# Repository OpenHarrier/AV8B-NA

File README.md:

# AV8B-NA
Files for the AV-8B N/A

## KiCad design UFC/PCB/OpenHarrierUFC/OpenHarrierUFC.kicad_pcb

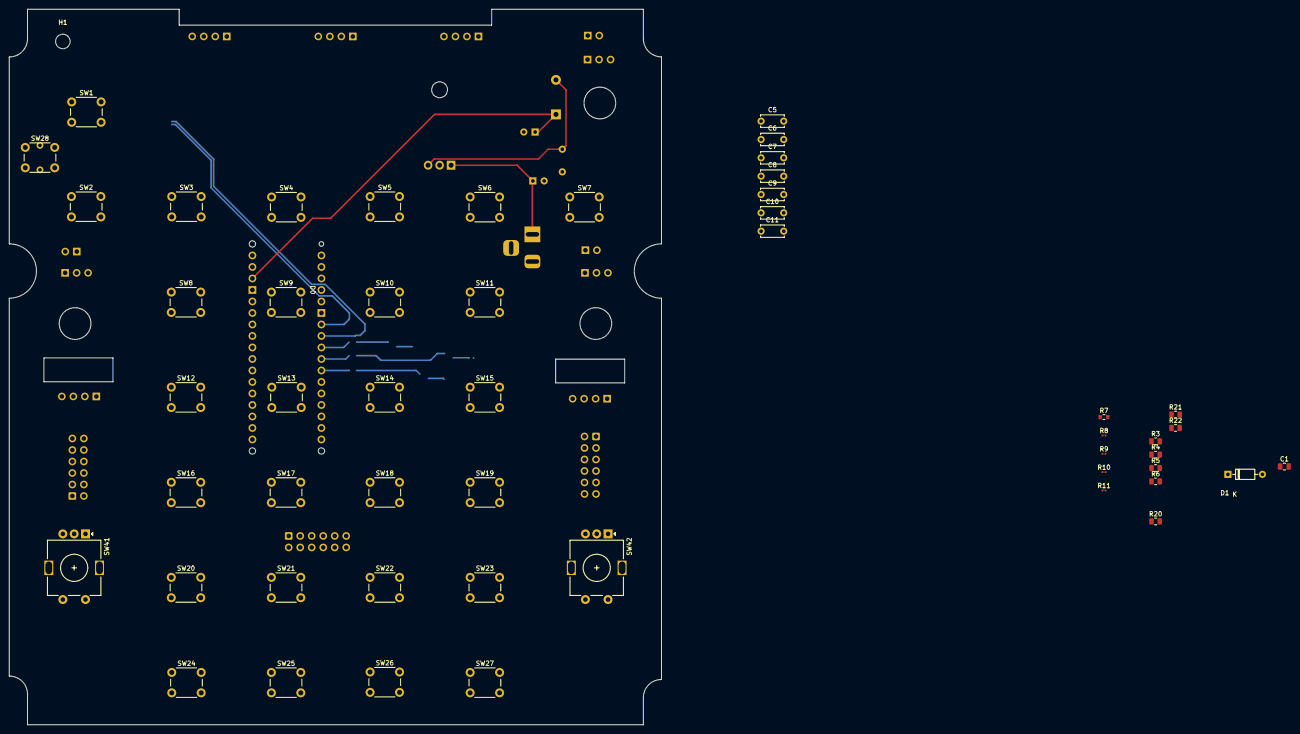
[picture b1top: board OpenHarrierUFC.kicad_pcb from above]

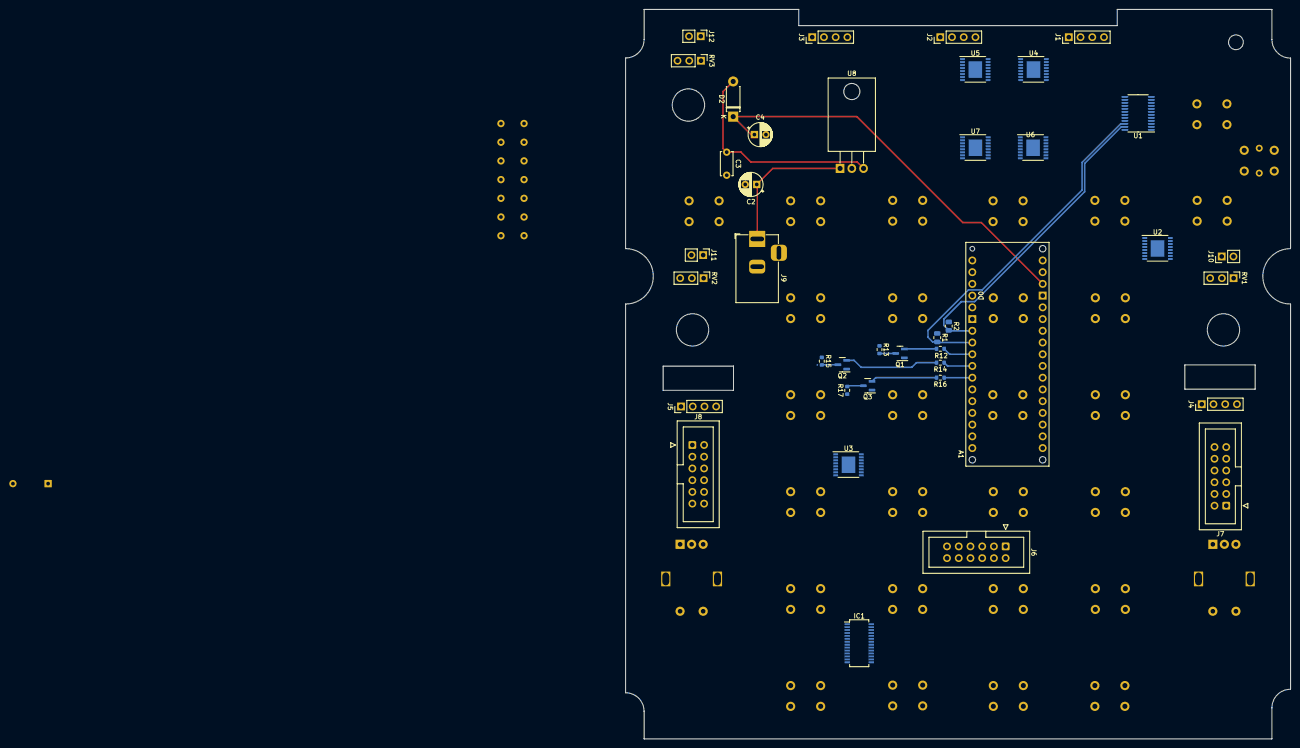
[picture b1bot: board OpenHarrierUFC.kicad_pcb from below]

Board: 2 copper layers, 144.0 x 158.0 mm, 92 parts (40 on the bottom side), 97 nets.

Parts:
A1: Arduino_Micro_Socket
C1: 10uF; C_0805_2012Metric
C2, C4: 100 uF; CP_Radial_D5.0mm_P2.50mm
C3, C5, C6, C7, C8, C9, C10, C11: 100 nF; C_Disc_D5.0mm_W2.5mm_P5.00mm
D1: 1N4148; D_DO-35_SOD27_P7.62mm_Horizontal
D2: 1N5819; D_DO-41_SOD81_P7.62mm_Horizontal
H1: MountingHole; MountingHole_3.2mm_M3
IC1: HT16K33-28SOP; SSOP-28_3.9x9.9mm_P0.635mm
J1: SCRATCHPAD1; PinHeader_1x04_P2.54mm_Vertical
J2: SCRATCHPAD2; PinHeader_1x04_P2.54mm_Vertical
J3: SCRATCHPAD3; PinHeader_1x04_P2.54mm_Vertical
J4, J5: Conn_01x04_Pin; PinHeader_1x04_P2.54mm_Vertical
J6: HUD PANEL; IDC-Header_2x06_P2.54mm_Vertical
J7: LEFT ANNUN; IDC-Header_2x06_P2.54mm_Vertical
J8: RIGHT ANNUN; IDC-Header_2x06_P2.54mm_Vertical
J9: Barrel_Jack_Switch; BarrelJack_Horizontal
J10: COMM1 ON/OFF; PinHeader_1x02_P2.54mm_Vertical
J11: COMM2 ON/OFF; PinHeader_1x02_P2.54mm_Vertical
J12: SCRTCH ON/OFF; PinHeader_1x02_P2.54mm_Vertical
Q1, Q2, Q3: 2N3904; SOT-23
R1, R2, R4, R5, R6: 10k; R_0805_2012Metric
R3: R; R_0805_2012Metric
R7: 2k2; R_0603_1608Metric
R8, R9, R10, R11: 2k2; R_0201_0603Metric
R12, R14, R16: 10k; R_0603_1608Metric
R13, R15, R17: 1k; R_0603_1608Metric
R20, R21, R22: 47K; R_0805_2012Metric
RV1, RV2, RV3: 10k; PinHeader_1x03_P2.54mm_Vertical
SW1, SW2, SW3, SW4, SW5, SW6, SW7, SW8, SW9, SW10, SW11, SW12, SW13, SW14, SW15, SW16, SW17, SW18, SW19, SW20, SW21, SW22, SW23, SW24, SW25, SW26, SW27: SW_Push; SW_PUSH_6mm
SW28: SW_Push_LED; SW_PUSH_6mm
SW41: COMM1 Encoder; RotaryEncoder_Alps_EC11E-Switch_Vertical_H20mm
SW42: COMM2 Encoder; RotaryEncoder_Alps_EC11E-Switch_Vertical_H20mm
U1: TCA9548APWR; TSSOP-24_4.4x7.8mm_P0.65mm
U2, U3, U4, U5, U6, U7: 4051; TSSOP-16-1EP_4.4x5mm_P0.65mm
U8: LM7805_TO220; TO-220-3_Horizontal_TabDown

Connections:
+3V3: R7.1, R8.1, R9.1, R10.1, R11.1
+5V: A1.VIN, C4.1, C5.1, C6.1, C7.1, C8.1, C9.1, C10.1, C11.1, D2.1 (K), IC1.28 (VDD), R13.1, R15.1, R17.1, U2.16 (VDD), U3.16 (VDD), U4.16 (VDD), U5.16 (VDD), U6.16 (VDD), U7.16 (VDD)
ADC0: A1.A0, U7.3 (X)
ADC_BRT: J6.3, U7.1 (X4)
ADC_CON: J6.4, U7.2 (X6)
ADC_SYM: J6.1, U7.12 (X3)
BUTTON1: A1.D7 (D7_INT4), R7.2, U2.3 (X)
BUTTON2: A1.D8, R8.2, U3.3 (X)
BUTTON3: A1.D9, R9.2, U4.3 (X)
BUTTON4: A1.D10, R10.2, U5.3 (X)
BUTTON5: A1.D11, R11.2, U6.3 (X)
CTRLA: Q1.3 (C), R13.2, U2.11 (A), U3.11 (A), U4.11 (A), U5.11 (A), U6.11 (A), U7.11 (A)
CTRLB: Q2.3 (C), R15.2, U2.10 (B), U3.10 (B), U4.10 (B), U5.10 (B), U6.10 (B), U7.10 (B)
CTRLC: Q3.3 (C), R17.2, U2.9 (C), U3.9 (C), U4.9 (C), U5.9 (C), U6.9 (C), U7.9 (C)
GND: C1.1, C2.2, C3.2, C4.2, C5.2, C6.2, C7.2, C8.2, C9.2, C10.2, C11.2, IC1.1 (VSS), J1.4, J2.4, J3.4, J4.4, J5.4, J6.7, J7.7, J8.7, J9.2, J10.2, J11.2, J12.2, Q1.1 (E), Q2.1 (E), Q3.1 (E), R4.1, R5.1, R6.1, RV1.1, RV2.1, RV3.1, SW1.1, SW2.1, SW3.1, SW4.1, SW5.1, SW6.1, SW7.1, SW8.1, SW9.1, SW10.1, SW11.1, SW12.1, SW13.1, SW14.1, SW15.1, SW16.1, SW17.1, SW18.1, SW19.1, SW20.1, SW21.1, SW22.1, SW23.1, SW24.1, SW25.1, SW26.1, SW27.1, SW41.S2, SW42.S2, U1.12 (GND), U2.6 (Inh), U2.7 (VEE), U2.8 (VSS), U3.6 (Inh), U3.7 (VEE), U3.8 (VSS), U4.6 (Inh), U4.7 (VEE), U4.8 (VSS), U5.6 (Inh), U5.7 (VEE), U5.8 (VSS), U6.6 (Inh), U6.7 (VEE), U6.8 (VSS), U7.6 (Inh), U7.7 (VEE), U7.8 (VSS), U8.2 (GND)
LCOM0: D1.2 (A), IC1.2 (COM0/AD), J7.10
LCOM1: IC1.3 (COM1/KS0), J7.9
LCOM2: IC1.4 (COM2/KS1), J8.10
LCOM3: IC1.5 (COM3/KS2), J8.9
LROW0: IC1.25 (ROW0/A2), J7.1, J8.1, R20.1
LROW1: IC1.24 (ROW1/A1), J7.2, J8.2, R21.1
LROW2: IC1.23 (ROW2/A0), J7.3, J8.3, R22.2
LROW3: IC1.22 (ROW3/K1), J7.4, J8.4
LROW4: IC1.21 (ROW4/K2), J7.5, J8.5
LROW5: IC1.20 (ROW5/K3), J7.6, J8.6
LROW6: IC1.19 (ROW6/K4), J7.12, J8.12
LROW7: IC1.18 (ROW7/K5), J7.11, J8.11
unnamed: D1.1 (K), R20.2, R21.2, R22.1
unnamed: C3.1, D2.2 (A), U8.3 (VO)
unnamed: J1.1, U1.4 (SD0)
unnamed: J1.2, U1.5 (SC0)
unnamed: J2.1, U1.6 (SD1)
unnamed: J2.2, U1.7 (SC1)
unnamed: J3.1, U1.8 (SD2)
unnamed: J3.2, U1.9 (SC2)
unnamed: J4.1, U1.10 (SD3)
unnamed: J4.2, U1.11 (SC3)
unnamed: J5.1, U1.13 (SD4)
unnamed: J5.2, U1.14 (SC4)
unnamed: Q1.2 (B), R12.2
unnamed: Q2.2 (B), R14.2
unnamed: Q3.2 (B), R16.2
unnamed: R6.2, U1.1 (A0)
unnamed: R5.2, U1.2 (A1)
unnamed: R4.2, U1.21 (A2)
unnamed: R3.2, U1.3 (~RESET)
unnamed: SW3.2, U2.13 (X0)
unnamed: SW2.2, U2.14 (X1)
unnamed: SW1.2, U2.15 (X2)
unnamed: SW4.2, U2.12 (X3)
unnamed: SW5.2, U2.1 (X4)
unnamed: SW8.2, U2.5 (X5)
unnamed: SW6.2, U2.2 (X6)
unnamed: SW7.2, U2.4 (X7)
unnamed: SW11.2, U3.13 (X0)
unnamed: SW10.2, U3.14 (X1)
unnamed: SW9.2, U3.15 (X2)
unnamed: SW12.2, U3.12 (X3)
unnamed: SW13.2, U3.1 (X4)
unnamed: SW16.2, U3.5 (X5)
unnamed: SW14.2, U3.2 (X6)
unnamed: SW15.2, U3.4 (X7)
unnamed: SW19.2, U4.13 (X0)
unnamed: SW18.2, U4.14 (X1)
unnamed: SW17.2, U4.15 (X2)
unnamed: SW20.2, U4.12 (X3)
unnamed: SW21.2, U4.1 (X4)
unnamed: SW24.2, U4.5 (X5)
unnamed: SW22.2, U4.2 (X6)
unnamed: SW23.2, U4.4 (X7)
unnamed: SW25.2, U5.13 (X0)
unnamed: SW26.2, U5.14 (X1)
unnamed: SW27.2, U5.15 (X2)
unnamed: RV3.2, U7.13 (X0)
unnamed: RV2.2, U7.14 (X1)
unnamed: RV1.2, U7.15 (X2)
unnamed: C2.1, J9.1, U8.1 (VI)
SCL: A1.D3 (D3/SCL), IC1.26 (SCL), R1.2, U1.22 (SCL)
SDA: A1.D2 (D2/SDA), IC1.27 (SDA), R2.2, U1.23 (SDA)
SEL0: A1.D4, R12.1
SEL1: A1.D5, R14.1
SEL2: A1.D6, R16.1
SW_BARO: J6.10, U6.4 (X7)
SW_C1ON: J10.1, U5.5 (X5)
SW_C2ON: J11.1, U5.2 (X6)
SW_COMM1: SW41.S1, U5.12 (X3)
SW_COMM2: SW42.S1, U5.1 (X4)
SW_DAY: J6.12, U6.5 (X5)
SW_MC: J7.8, U6.13 (X0)
SW_MW: J8.8, U6.14 (X1)
SW_NGT: J6.11, U6.2 (X6)
SW_NORM: J6.5, U6.12 (X3)
SW_REJ2: J6.6, U6.1 (X4)
SW_SCRTCH: J12.1, U5.4 (X7)
SW_SYM: J6.2, U6.15 (X2)
VCC: C1.2, J1.3, J2.3, J3.3, J4.3, J5.3, R1.1, R2.1, R3.1, U1.24 (VCC)
VREF: J6.8, RV1.3, RV2.3, RV3.3

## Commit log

2023-07-27 Initial upload of files to new official OpenHarrier repo
2023-09-25 Initial upload of Greg Sabin's models
    These models were contributed by OpenHarrier member Greg Sabin.
2023-09-25 Documentation files migrated from old repository
2023-10-01 Initial upload of Jason Tatum's SJU-4A ejection seat model
    Initial upload of Jason Tatum's SJU-4A ejection seat model. Build instructions document coming soon.
2023-10-01 Initial draft of construction plans
    Uploading a draft of construction plans (which are incomplete). Also added a couple of technical drawings to the FreeCAD model.
2023-11-29 Complete rework of the HUD base and HUD frames
    Includes the original FreeCAD model as well as STL files for a single part base and single part left and right frames, as well as sliced (split) parts for base and frame for those that have smaller 3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
2024-05-09 Initial release of WIP official OpenHarrier model
    Initial release of the official WIP OpenHarrier model, designed in FreeCAD 0.21.2.
2024-05-09 Update README.md
    Added a disclaimer
2024-05-09 Update README.md
    Added a note about the gear errors that appear in the report view.
2024-08-03 UFC updates
    General work on updating the UFC.
2024-08-03 Initial (WIP) design work on the UFC PCB
    Note that I've only just begun laying down the traces on the PCB. This board is NOT ready for production!
2024-08-03 Modeled outer dimensions of HSI Mk.1 throttle box
    Modeled the outer dimensions of the HSI Mk.1 throttle box to see what modifications would be needed to the left console / left console platform to make it fit. Will require opening up a slot in the l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
2024-08-04 Update .gitignore to ignore PrivateReferenceModels
    These are reference models that I have purchased and cannot upload to a public repo as I have no rights to do that with these files.
2024-08-10 Reworked left and right consoles.
    Reworked left and right consoles. Note that this is still a work in progress. I need to design 3D printed brackets for between the upper frame members and for providing mounting solutions to the pane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
2024-08-19 More work on the left console structure
    Designed a draft for the 3D printed parts that will hold the left console panels. This is a WIP and still needs screw holes, final alignments, and broken up into several different sections that snap 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
2024-08-22 Got Dzus rail holes lined up on left consoles, created new parametric panels based on Dzus formulas.
2024-08-28 More updates to left console panel and panel frame. Still a WIP.
2024-08-28 Hid some parts that need to be removed.
    Hid some old parts that need to be removed.
2024-09-02 Worked on UFC body parts to get them ready for printing
    Lots of work to get parts ready for 3D printing. The mounting bodies now have proper holes for threaded inserts. Added tabs to the upper rear piece that will mount to the HUD assembly / HUD.
2024-09-02 Added STL files for the first 2 parts of the UFC since I've now printed those.
2024-09-08 More work on the UFC
    Added some STL files for parts that I've actually 3d printed.
2024-09-12 More UFC work
2024-09-30 UFC Updates
    Lots of updates to the UFC. Created updated STL files for all of the UFC parts I have printed so far.
2024-11-22 Various model updates
    FreeCAD 1.0.0 is now the standard version we are using.
2025-01-20 Various work on HUD and rework of ODU parts
2025-01-21 Working on engine panel. Fixed sizing of button holes on ODU and removed extra support for SSD1306
2025-01-21 Fixed some alignment issues with parts of the ODU v2. Added displays, lenses, and buttons for all 5 ODU positions.
2025-01-21 Fixed size of button holes, which was still too small!
2025-02-08 Initial release of MasterArm panel
    Initial release of MasterArm panel. Still working on the SVG's for laser cutting and engraving.
2025-02-08 Added master file for engraving & laser cutting.
2025-02-09 Updates to MasterArm Panel, ODU panel, and Main Panel
    Moved MasterArm and ODU assemblies to be sub-assemblies of MainPanel instead of the main model. This makes it easier to work on these without having to load the entire cockpit model. Started work on 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
2025-02-22 Initial checkin of ACP panel
2025-03-02 Fuel Panel completed
2025-03-03 Added SVG cross-sections of fuel panel for laser cutting and engraving.
2025-03-09 Engine Panel initial checkin
    Engine panel initial checkin.
2025-03-09 Updated which items are shown and unshown
2025-03-10 Finished off knobs and slight adjustment to servo position on engine panel
    Knobs are ready for 3d printing. Adjusted servo position on the OLED/Servo Tray as it was off by a bit.
2025-03-10 Work started on Airspeed instrument
2025-03-25 Attitude indicator initial upload (WIP)
    Things remaining to do: Model the hall effect sensors, model the reference line mechanism, model the final pitch drum attachments, model the pull-to-cage switch, and model the animations in Assembly 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
2025-03-25 Update Attitude-Indicator.FCStd
    Minor updates to colors
2025-03-27 Reorganized sub-parts
    Reorganized the sub-parts so that they can easily be hidden or shown as sub-assemblies as desired.
2025-03-27 Update MasterArmPanelBody.FCStd
    Fixed the visibility on some of the panels that gotten hidden for some unknown reason.
2025-03-30 Completed all the assembly animations
    Added all of the sub-assembly animations. Double-click the assembly object, and you should be able to click and drag on the different moving parts to see them animate.
2025-03-30 Added hall effect sensors to roll and pitch
    Added the hall effect sensors and magnets to the roll and pitch
2025-04-06 Numerous updates to attitude indicator
    Numerous updates made after making adjustments due to part fitment problems or resolutions to various problems. Note that this instrument is still a work in progress, probably needing another week of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
2025-04-15 Updates to Pedestal, adding top-faces of other standby instruments
2025-05-02 Numerous updates
    Lots of stuff being updated...
2025-07-01 Lots of main panel and pedestal updates
    Added or updated cutouts to the main panel and pedestal. Completed some of the panel models for the pedestal. Revised the WIP model for the ECM panel. Adjusted position of engine panel.
2025-07-16 Lots of updates and SVG and STL files for main instrument and and pedestal panels.
2025-07-26 Reworked master caution & master warn buttons
    Reworked the mechanism inside master caution and master warn bodies to accommodate the key switches. Also WIP on reworking the station selector buttons on the ACP. I think I thought I had designed th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
2025-07-27 Added Arduino code for fuel panel and added a backplate to hold the OLED displays in
    Initial release of the fuel panel Arduino code with number drums. There are 3 things missing from the Arduino code as I have not yet implemented these parts:
    Selector knob (7 position rotary switch), bingo knob (rotary encoder), and fuel on/off indicator light. Those things will be added in the near future as I implement them on my panel.
2025-07-27 Updated master caution / master warn 3d printed body again for LED revisions
    Updated the body to allow for easier mounting of 5mm LED's.
2025-07-31 Updates to MASTER HUD modes
    Completely revised the parts for the master hud mode buttons to solve for some mechanical issues. Also revised the outer body for the flare salvo button to allow easier access to the pins on the key 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
2025-07-31 Added an optional mouse table
    This is a first draft for a "mouse table" to serve as a flat surface to operate a mouse on. This can be mirrored to work on either side of the cockpit.
2025-08-05 Lots of updates
    Lots of revisions based on knowledge gained from actually building parts.
2025-08-10 Create OpenHarrier_ResetDCS_BIOS_BadData.ino
    Add this code to only 1 of your Arduino sketches to fix the issue with the canopy flood lights from generating 100's of errors per second in DCS-BIOS.log which decreases the performance of DCS-BIOS.
2025-12-28 Arming handle for ejection seat
2025-12-28 Added m2 parts for mounting switch
2025-12-28 Updated assembly order notes
2026-01-07 Ejection Seat Ejection Pull mechanism
2026-01-19 Initial draft of Annunciator panel that goes on right corner console
2026-01-20 Fixed a bunch of parts that had become corrupted. Now recomputes perfectly!
2026-01-20 Removed old ejection pulll handle
2026-01-21 Resized panel based on actual measurements received. Thanks, Boggy!
2026-01-21 Adjusted darkness of lens on annunciator body
2026-01-21 Fixed an error on the tray, also produced a second version of the annunciator body (slanted)
2026-01-22 Scaled the width and height down slightly (.1mm) for a better fit on panel and tray
2026-01-22 Adjusted position of straight annunciator body to account for the slightly smaller size
2026-01-22 Updates to headrest pole parts
2026-02-11 Numerous updates. Much of it is a work in progress.
2026-02-15 Updated version and created STL file.
2026-03-15 Lots of panel updates
2026-03-25 Prepping for upgrade to FreeCAD 1.1 release
    Quick checkin of everything before upgrading to FreeCAD 1.1 release version.
2026-04-02 First working version of the landing gear knob!
    You'll need a spring at the end and a contact leaf spring.
2026-04-02 Switched text to be embossed instead of cut / engraved
2026-04-02 Some adjustments to the corner consoles
2026-04-02 Finally fixed the glitch with the glareshield.
    Apparently one of the surfaces got deleted, resulting in corruption of downstream steps. This has been fixed, finally!
2026-05-22 Lots of updates
2026-05-22 Removed old ODU folder and added a couple of missing files
2026-05-22 Removed old WIP PCB stuff for UFC
    I removed WIP PCB stuff that had been imported from KiCAD. At this point, I'm going to defer designing a PCB for the UFC as something I might do way down the road. In interim, I'm planning on manuall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
2026-06-23 Added Arduino code to repo
2026-06-23 Various updates
2026-06-25 Attempting to fix the main model and the partially loaded documents issue
    I am working on rebuilding the parent document for the OpenHarrier model, which for now is temporarily named "AV8B-NA-FreeCad1-1.FCStd. There will be some errors about some documents only partially l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
2026-06-27 HUGE refactor.
    HUGE refactor. We've flatted the FreeCAD file structure so that all of the FreeCAD files are now in the same directory, organized by name, either starting with "Section-", "Panel-", or "Part-". The m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
